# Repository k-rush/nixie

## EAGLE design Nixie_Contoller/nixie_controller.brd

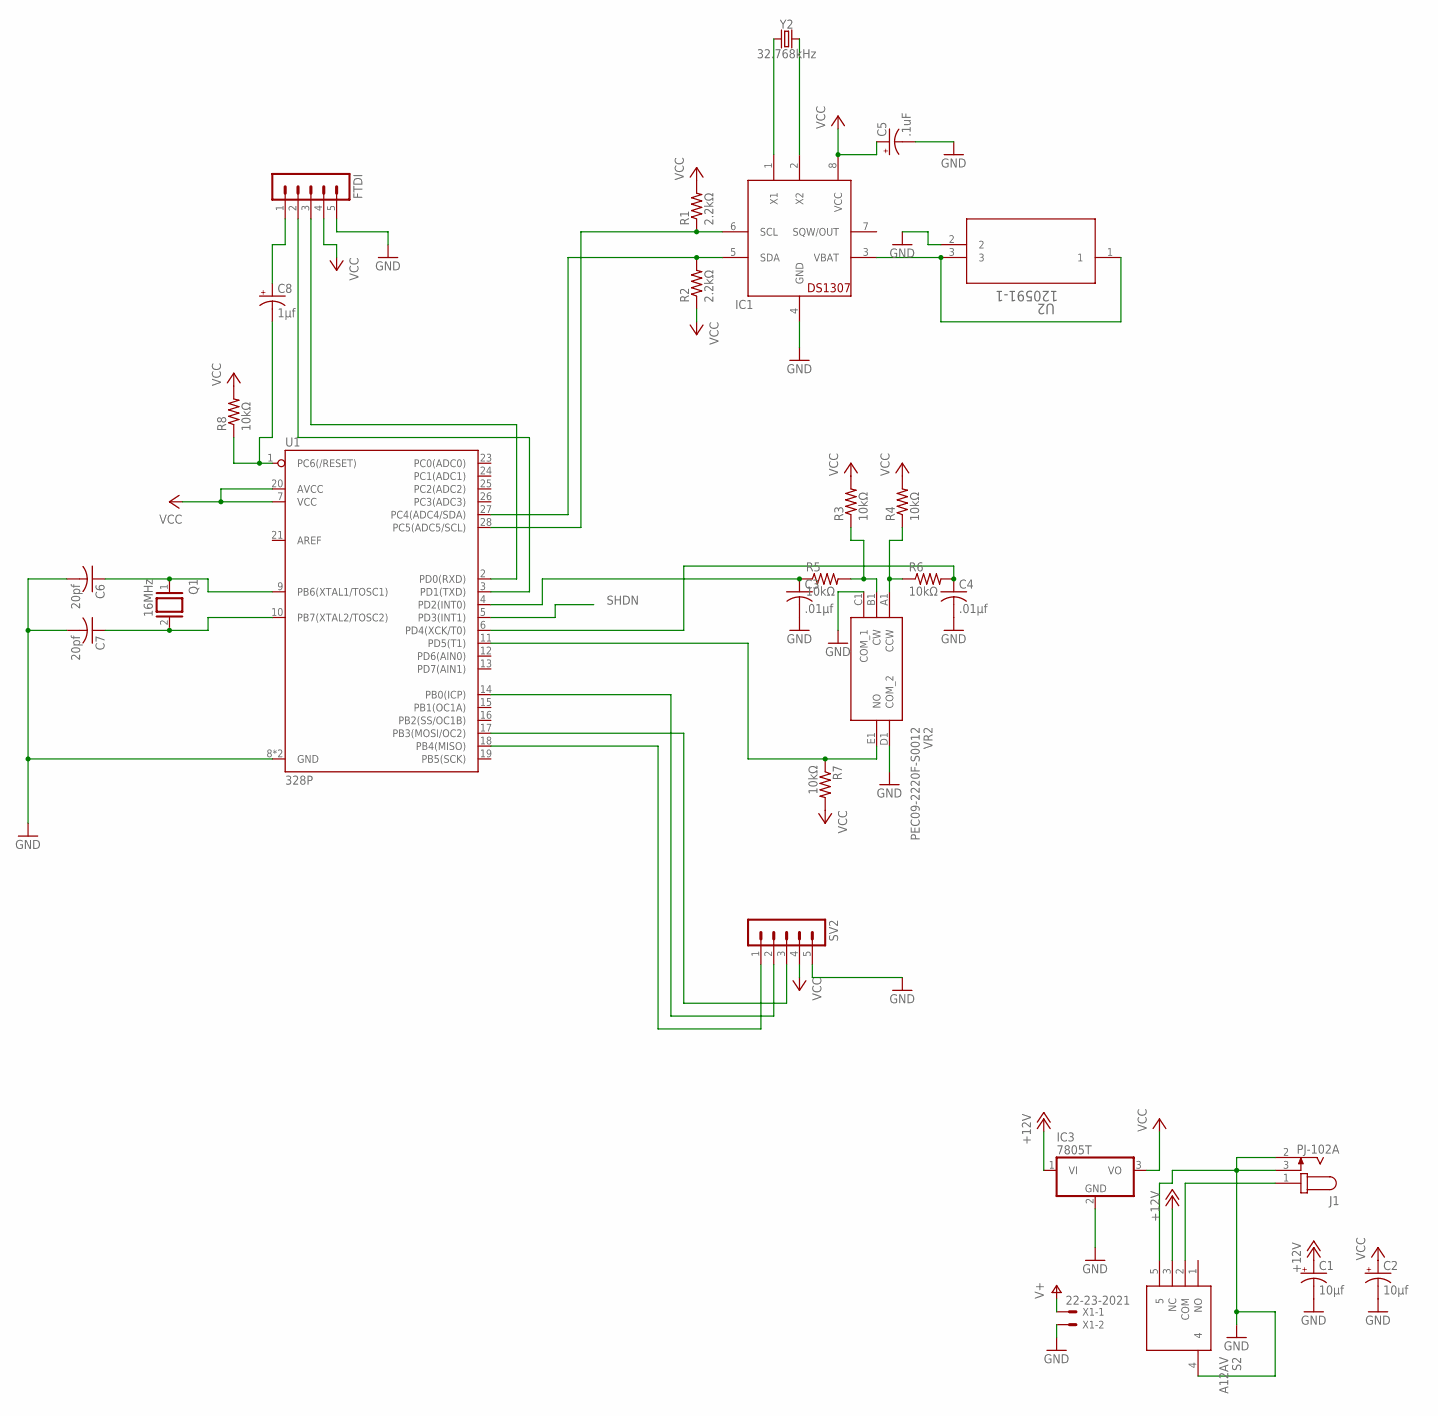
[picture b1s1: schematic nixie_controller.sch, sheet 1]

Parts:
C1, C2: 10μf; E2-5
C3, C4: .01μf; C050-030X075
C5: .1uF; E2-5
C6, C7: 20pf; C050-030X075
C8: 1μf; E2-5
FTDI: MA05-1
IC1: DS1307; DIL08
IC3: 7805T; TO220H
J1: PJ-102A; CUI_PJ-102A
Q1: 16MHz; QS
R1, R2: 2.2kΩ; 0207/10
R3, R4, R5, R6, R7, R8: 10kΩ; 0207/10
S2: A12AV
SV2: MA05-1
U1: 328P; DIP28
U2: 120591-1; CONN3_120591-1
VR2: PEC09-2220F-S0012; PEC092220FS0012
X1: 22-23-2021
Y2: 32.768kHz; CRYSTAL-PTH-2X6-CYL

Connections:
+12V: C1.+, IC3.1 (VI), S2.3 (NC); also elsewhere on the board
CLK: SV2.1, U1.18 (PB4(MISO))
GND: C1.-, C2.-, C3.2, C4.2, C5.-, C6.2, C7.2, FTDI.5, IC1.4 (GND), IC3.2 (GND), J1.2, J1.3, S2.4, S2.5, SV2.5, U1.8 (GND), U1.22 (GND), U2.2, VR2.C1 (COM_1), VR2.D1 (COM_2), X1.2; also elsewhere on the board
unnamed: IC1.3 (VBAT), U2.1, U2.3
unnamed: R7.1, U1.11 (PD5(T1)), VR2.E1 (NO)
unnamed: R4.1, R6.1, VR2.A1 (CCW)
unnamed: IC1.1 (X1), Y2.1
unnamed: IC1.2 (X2), Y2.2
unnamed: J1.1, S2.2 (COM)
unnamed: SV2.2, U1.14 (PB0(ICP))
unnamed: C3.1, R5.1, U1.4 (PD2(INT0))
unnamed: C4.1, R6.2, U1.6 (PD4(XCK/T0))
unnamed: C6.1, Q1.1, U1.9 (PB6(XTAL1/TOSC1))
unnamed: IC1.6 (SCL), R1.1, U1.28 (PC5(ADC5/SCL))
unnamed: IC1.5 (SDA), R2.2, U1.27 (PC4(ADC4/SDA))
unnamed: C8.-, R8.1, U1.1 (PC6(/RESET))
unnamed: R3.1, R5.2, VR2.B1 (CW)
unnamed: C7.1, Q1.2, U1.10 (PB7(XTAL2/TOSC2))
unnamed: C8.+, FTDI.1
unnamed: SV2.3, U1.17 (PB3(MOSI/OC2))
unnamed: FTDI.2, U1.3 (PD1(TXD))
unnamed: FTDI.3, U1.2 (PD0(RXD))
SHDN: U1.5 (PD3(INT1)); also elsewhere on the board
V+: X1.1; also elsewhere on the board
VCC: C2.+, C5.+, FTDI.4, IC1.8 (VCC), IC3.3 (VO), R1.2, R2.1, R3.2, R4.2, R7.2, R8.2, SV2.4, U1.7 (VCC), U1.20 (AVCC)

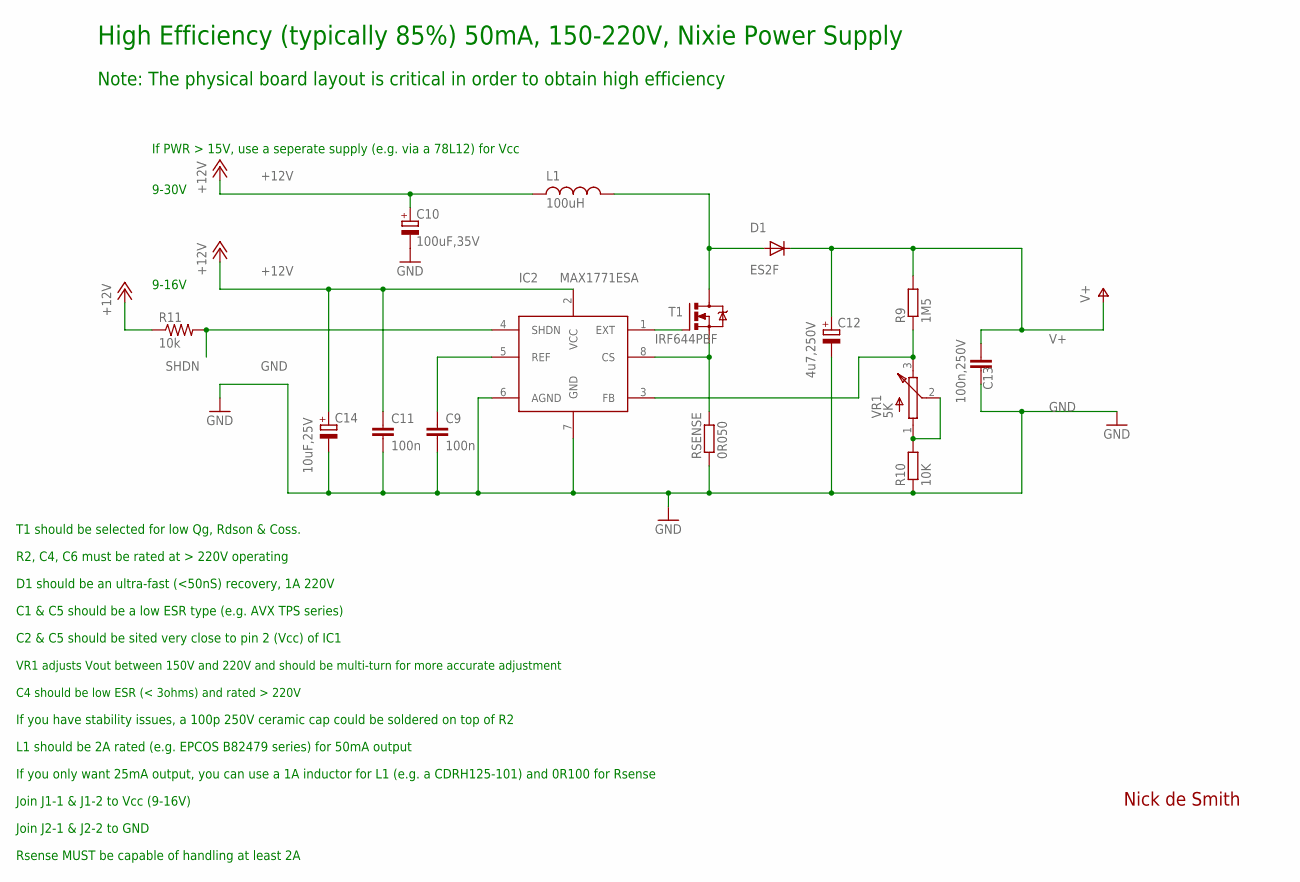
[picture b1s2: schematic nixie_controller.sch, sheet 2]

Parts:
C9, C11: 100n; C0805
C10: 100uF,35V; C-EIA-7343
C12: 4u7,250V; NICHICON-UJ-12
C13: 100n,250V; C2420
C14: 10uF,25V; C-EIA-7343
D1: ES2F; SMC
IC2: MAX1771ESA; SO-8
L1: 100uH; L-B82479
R9: 1M5; R2512
R10: 10K; R0805
R11: 10k; M0805
RSENSE: 0R050; R2010
T1: IRF644PBF; TO220BV
VR1: 5K; BOURNS-3214W

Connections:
+12V: C10.+, C11.1, C14.+, IC2.2 (VCC), L1.P$1 (1), R11.1; also elsewhere on the board
EXT: IC2.1 (EXT), T1.G
GND: C9.2, C10.-, C11.2, C12.1 (-), C13.P$2 (2), C14.-, IC2.6 (AGND), IC2.7 (GND), R10.1, RSENSE.1; also elsewhere on the board
unnamed: IC2.3 (FB), R9.1, VR1.3 (B)
unnamed: D1.A, L1.P$2 (2), T1.D
unnamed: C9.1, IC2.5 (REF)
unnamed: R10.2, VR1.1 (A), VR1.2 (W)
unnamed: IC2.8 (CS), RSENSE.2, T1.S
SHDN: IC2.4 (SHDN), R11.2; also elsewhere on the board
V+: C12.2 (+), C13.P$1 (1), D1.C, R9.2; also elsewhere on the board

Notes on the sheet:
R2, C4, C6 must be rated at > 220V operating
D1 should be an ultra-fast (<50nS) recovery, 1A 220V
C1 & C5 should be a low ESR type (e.g. AVX TPS series)
C2 & C5 should be sited very close to pin 2 (Vcc) of IC1
Nick de Smith
VR1 adjusts Vout between 150V and 220V and should be multi-turn for more accurate adjustment
C4 should be low ESR (< 3ohms) and rated > 220V
If you have stability issues, a 100p 250V ceramic cap could be soldered on top of R2
L1 should be 2A rated (e.g. EPCOS B82479 series) for 50mA output
Join J1-1 & J1-2 to Vcc (9-16V)
Join J2-1 & J2-2 to GND
T1 should be selected for low Qg, Rdson & Coss.
Rsense MUST be capable of handling at least 2A
High Efficiency (typically 85%) 50mA, 150-220V, Nixie Power Supply
9-16V
9-30V
If PWR > 15V, use a seperate supply (e.g. via a 78L12) for Vcc
Note: The physical board layout is critical in order to obtain high efficiency
If you only want 25mA output, you can use a 1A inductor for L1 (e.g. a CDRH125-101) and 0R100 for Rsense

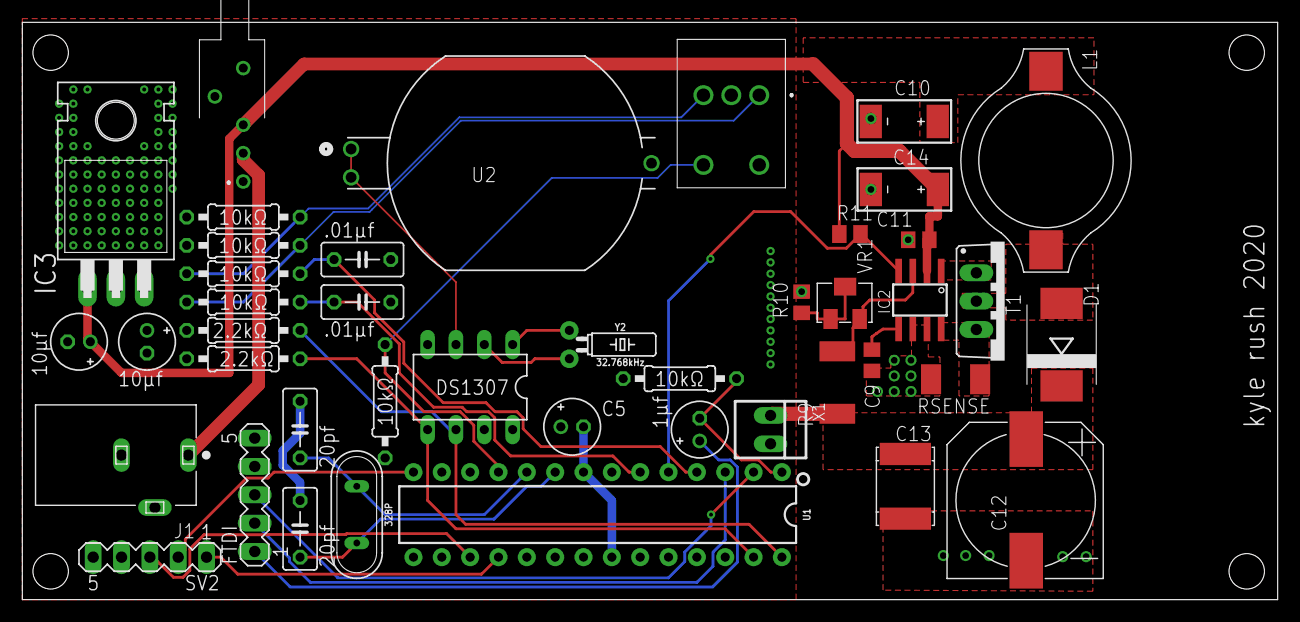
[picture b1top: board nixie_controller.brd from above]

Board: 2 copper layers, 112.5 x 51.7 mm, 43 parts (0 on the bottom side), 31 nets.

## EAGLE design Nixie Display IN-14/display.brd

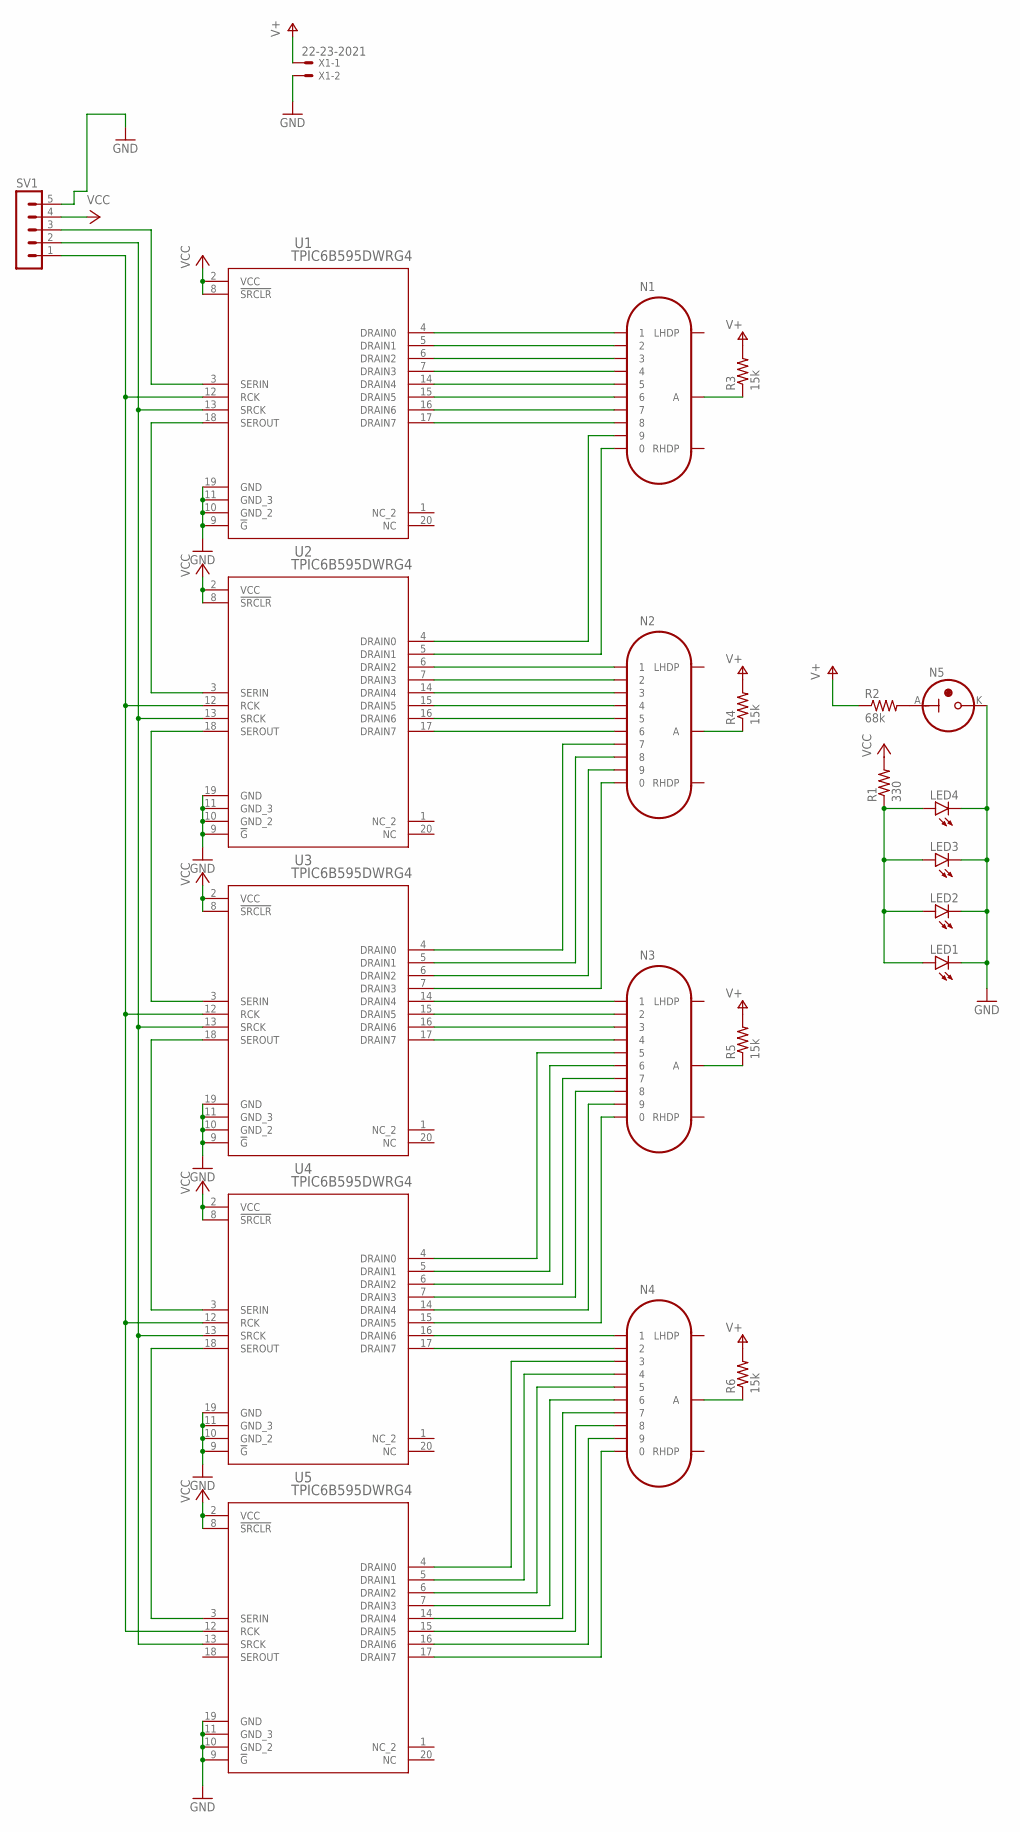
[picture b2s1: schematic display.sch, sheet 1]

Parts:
LED1, LED2, LED3, LED4: LED3MM
N1, N2, N3, N4: IN-14
N5: IN-3
R1: 330; R0805
R2: 68k; R0805
R3, R4, R5, R6: 15k; R0805
SV1: MA05-1
U1, U2, U3, U4, U5: TPIC6B595DWRG4; DW20
X1: 22-23-2021

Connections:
GND: LED1.K (C), LED2.K (C), LED3.K (C), LED4.K (C), N5.K, SV1.5, U1.9 (!G), U1.10 (GND_2), U1.11 (GND_3), U1.19 (GND), U2.9 (!G), U2.10 (GND_2), U2.11 (GND_3), U2.19 (GND), U3.9 (!G), U3.10 (GND_2), U3.11 (GND_3), U3.19 (GND), U4.9 (!G), U4.10 (GND_2), U4.11 (GND_3), U4.19 (GND), U5.9 (!G), U5.10 (GND_2), U5.11 (GND_3), U5.19 (GND), X1.2
unnamed: N1.1, U1.4 (DRAIN0)
unnamed: N1.2, U1.5 (DRAIN1)
unnamed: N1.3, U1.6 (DRAIN2)
unnamed: N1.4, U1.7 (DRAIN3)
unnamed: N1.5, U1.14 (DRAIN4)
unnamed: N1.6, U1.15 (DRAIN5)
unnamed: N1.7, U1.16 (DRAIN6)
unnamed: N1.8, U1.17 (DRAIN7)
unnamed: N1.9, U2.4 (DRAIN0)
unnamed: N1.0, U2.5 (DRAIN1)
unnamed: N2.1, U2.6 (DRAIN2)
unnamed: N2.2, U2.7 (DRAIN3)
unnamed: N2.3, U2.14 (DRAIN4)
unnamed: N2.4, U2.15 (DRAIN5)
unnamed: N2.5, U2.16 (DRAIN6)
unnamed: N2.6, U2.17 (DRAIN7)
unnamed: N2.7, U3.4 (DRAIN0)
unnamed: N2.8, U3.5 (DRAIN1)
unnamed: N2.9, U3.6 (DRAIN2)
unnamed: N2.0, U3.7 (DRAIN3)
unnamed: LED1.A, LED2.A, LED3.A, LED4.A, R1.1
unnamed: N5.A, R2.2
unnamed: N1.A, R3.1
unnamed: N2.A, R4.1
unnamed: N3.A, R5.1
unnamed: N4.A, R6.1
unnamed: U4.18 (SEROUT), U5.3 (SERIN)
unnamed: SV1.1, U1.12 (RCK), U2.12 (RCK), U3.12 (RCK), U4.12 (RCK), U5.12 (RCK)
unnamed: N3.1, U3.14 (DRAIN4)
unnamed: N3.2, U3.15 (DRAIN5)
unnamed: N3.3, U3.16 (DRAIN6)
unnamed: N3.4, U3.17 (DRAIN7)
unnamed: N3.8, U4.7 (DRAIN3)
unnamed: N3.6, U4.5 (DRAIN1)
unnamed: N3.9, U4.14 (DRAIN4)
unnamed: N3.5, U4.4 (DRAIN0)
unnamed: N3.7, U4.6 (DRAIN2)
unnamed: N3.0, U4.15 (DRAIN5)
unnamed: N4.1, U4.16 (DRAIN6)
unnamed: N4.2, U4.17 (DRAIN7)
unnamed: N4.0, U5.17 (DRAIN7)
unnamed: N4.9, U5.16 (DRAIN6)
unnamed: N4.8, U5.15 (DRAIN5)
unnamed: N4.7, U5.14 (DRAIN4)
unnamed: N4.6, U5.7 (DRAIN3)
unnamed: N4.5, U5.6 (DRAIN2)
unnamed: N4.4, U5.5 (DRAIN1)
unnamed: N4.3, U5.4 (DRAIN0)
unnamed: SV1.2, U1.13 (SRCK), U2.13 (SRCK), U3.13 (SRCK), U4.13 (SRCK), U5.13 (SRCK)
unnamed: SV1.3, U1.3 (SERIN)
unnamed: U1.18 (SEROUT), U2.3 (SERIN)
unnamed: U2.18 (SEROUT), U3.3 (SERIN)
unnamed: U3.18 (SEROUT), U4.3 (SERIN)
V+: R2.1, R3.2, R4.2, R5.2, R6.2, X1.1
VCC: R1.2, SV1.4, U1.2 (VCC), U1.8 (!SRCLR), U2.2 (VCC), U2.8 (!SRCLR), U3.2 (VCC), U3.8 (!SRCLR), U4.2 (VCC), U4.8 (!SRCLR), U5.2 (VCC), U5.8 (!SRCLR)

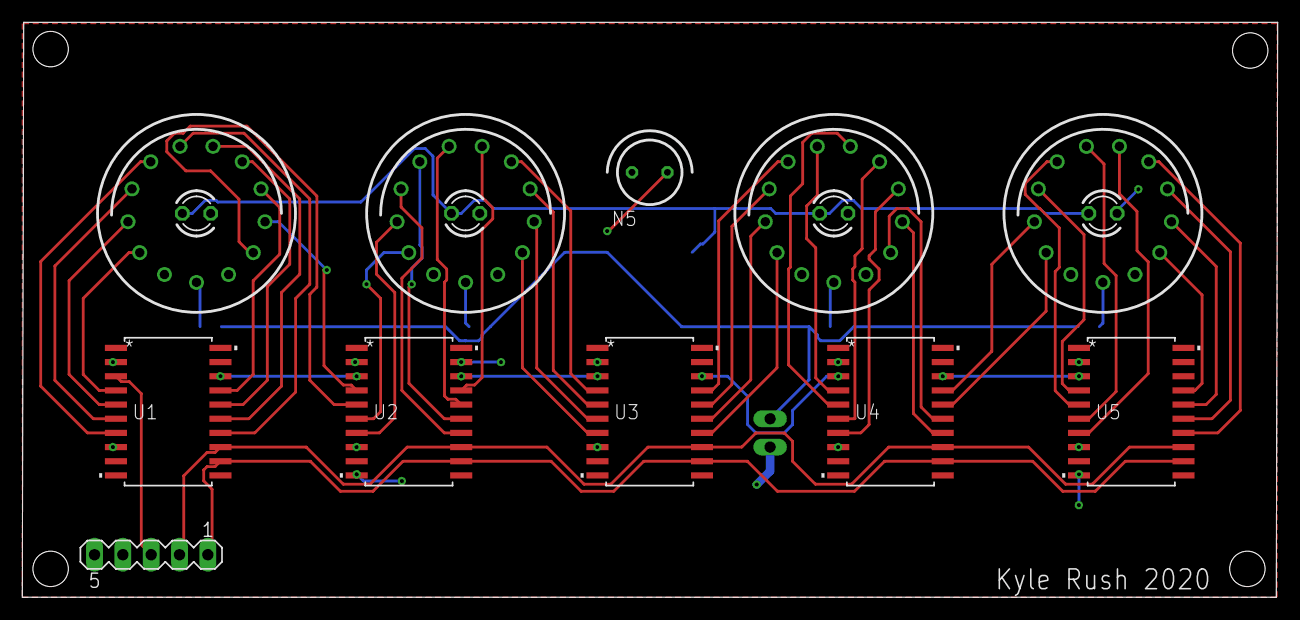
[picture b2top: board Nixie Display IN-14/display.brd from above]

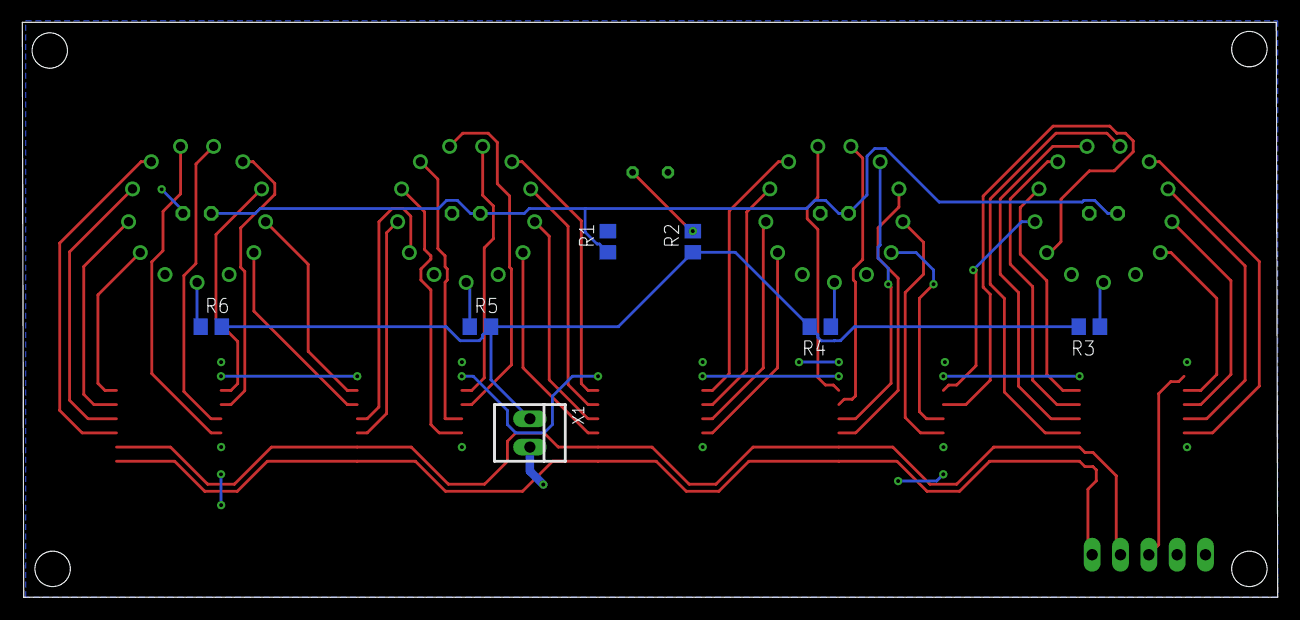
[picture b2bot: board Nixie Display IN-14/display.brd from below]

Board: 2 copper layers, 112.6 x 51.6 mm, 22 parts (7 on the bottom side), 56 nets.

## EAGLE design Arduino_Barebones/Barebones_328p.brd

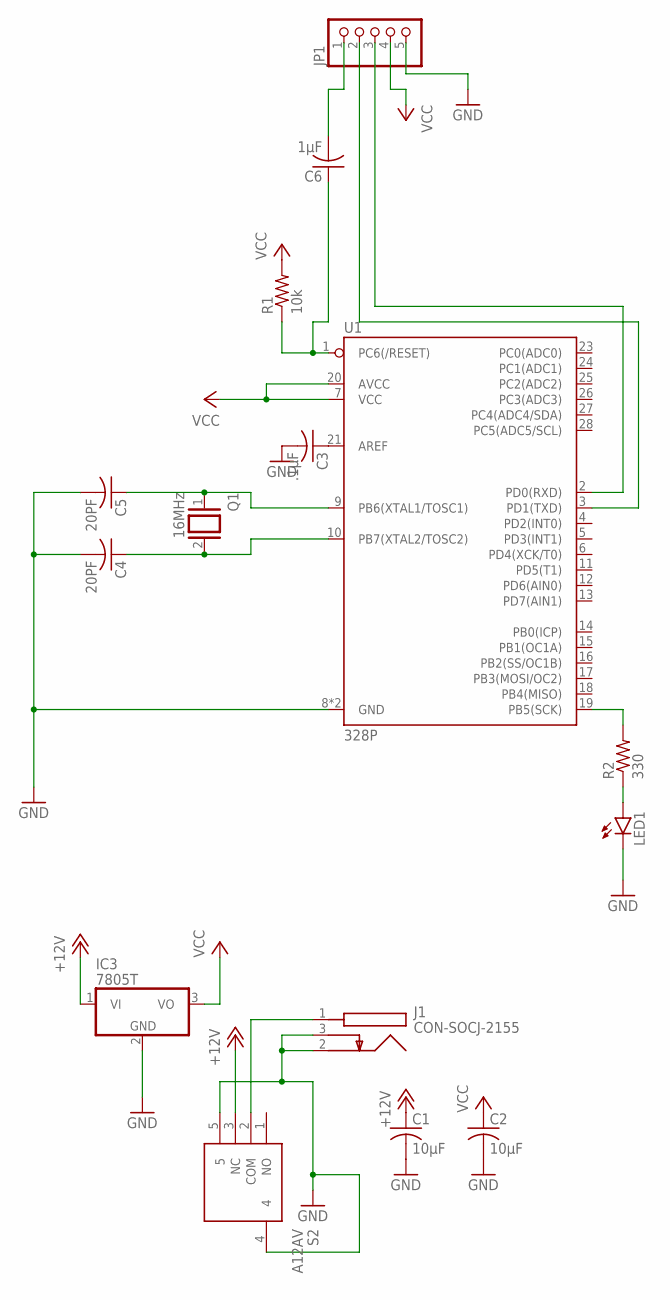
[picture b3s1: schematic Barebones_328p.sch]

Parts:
C1, C2: 10μF; C0603
C3: .1μF; C0603
C4, C5: 20PF; C0603
C6: 1μF; C0603
IC3: 7805T; TO220H
J1: CON-SOCJ-2155; CONSOCJ2155
JP1: PINHD-1X5; 1X05
LED1: LEDCHIP-LED0805; CHIP-LED0805
Q1: 16MHz; QS
R1: 10k; R0603
R2: 330; R0603
S2: A12AV
U1: 328P; DIP28

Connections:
+12V: C1.1, IC3.1 (VI), S2.3 (NC)
GND: C1.2, C2.2, C3.2, C4.2, C5.2, IC3.2 (GND), J1.2, J1.3, JP1.5, LED1.C, S2.4, S2.5, U1.8 (GND), U1.22 (GND)
unnamed: R2.2, U1.19 (PB5(SCK))
unnamed: LED1.A, R2.1
unnamed: J1.1, S2.2 (COM)
unnamed: C3.1, U1.21 (AREF)
unnamed: C5.1, Q1.1, U1.9 (PB6(XTAL1/TOSC1))
unnamed: C6.1, R1.1, U1.1 (PC6(/RESET))
unnamed: C4.1, Q1.2, U1.10 (PB7(XTAL2/TOSC2))
unnamed: C6.2, JP1.1
unnamed: JP1.2, U1.3 (PD1(TXD))
unnamed: JP1.3, U1.2 (PD0(RXD))
VCC: C2.1, IC3.3 (VO), JP1.4, R1.2, U1.7 (VCC), U1.20 (AVCC)

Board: 2 copper layers, 15 parts (0 on the bottom side), 13 nets, no tracks yet.

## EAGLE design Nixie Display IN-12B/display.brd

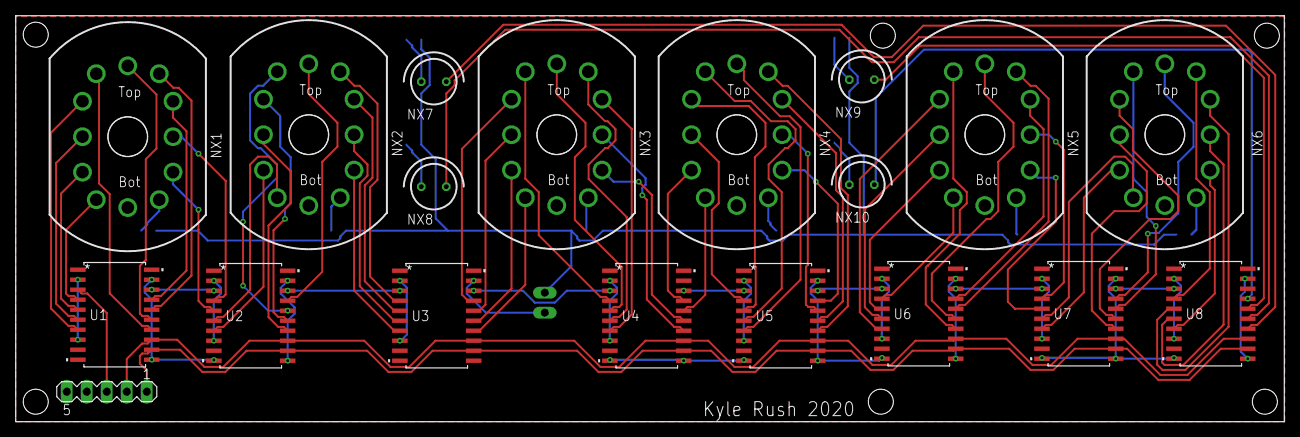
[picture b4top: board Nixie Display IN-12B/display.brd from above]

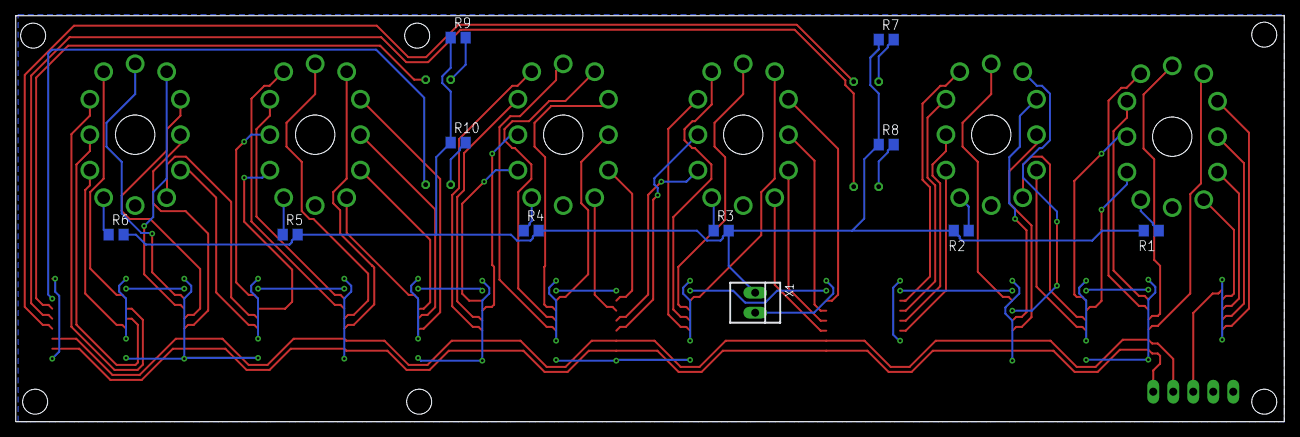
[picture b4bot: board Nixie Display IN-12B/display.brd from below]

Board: 2 copper layers, 161.1 x 51.6 mm, 30 parts (11 on the bottom side), 87 nets.

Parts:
NX1, NX2, NX3, NX4, NX5, NX6: IN-12-DSUB
NX7, NX8, NX9, NX10: IN-3
R1, R2, R3, R4, R5, R6: 15k; R0805
R7, R8, R9, R10: 68k; R0805
SV1: MA05-1
U1, U2, U3, U4, U5, U6, U7, U8: TPIC6B595DWRG4; DW20
X1: 22-23-2021

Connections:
GND: SV1.5, U1.9, U1.10, U1.11, U1.19, U2.9, U2.10, U2.11, U2.19, U3.9, U3.10, U3.11, U3.19, U4.9, U4.10, U4.11, U4.19, U5.9, U5.10, U5.11, U5.19, U6.9, U6.10, U6.11, U6.19, U7.9, U7.10, U7.11, U7.19, U8.9, U8.10, U8.11, U8.19, X1.2
unnamed: NX1.1, U1.4
unnamed: NX1.2, U1.5
unnamed: NX1.3, U1.6
unnamed: NX1.4, U1.7
unnamed: NX1.5, U1.14
unnamed: NX1.6, U1.15
unnamed: NX1.7, U1.16
unnamed: NX1.8, U1.17
unnamed: NX1.9, U2.4
unnamed: NX1.0, U2.5
unnamed: NX2.1, U2.6
unnamed: NX2.2, U2.7
unnamed: NX2.3, U2.14
unnamed: NX2.4, U2.15
unnamed: NX2.5, U2.16
unnamed: NX2.6, U2.17
unnamed: NX2.7, U3.4
unnamed: NX2.8, U3.5
unnamed: NX2.9, U3.6
unnamed: NX2.0, U3.7
unnamed: NX7.A, R7.2
unnamed: NX1.A, R1.1
unnamed: NX2.A, R2.1
unnamed: NX3.A, R3.1
unnamed: NX4.A, R4.1
unnamed: U4.18, U5.3
unnamed: SV1.1, U1.12, U2.12, U3.12, U4.12, U5.12, U6.12, U7.12, U8.12
unnamed: NX3.1, U3.14
unnamed: NX3.2, U3.15
unnamed: NX3.3, U3.16
unnamed: NX3.4, U3.17
unnamed: NX3.8, U4.7
unnamed: NX3.6, U4.5
unnamed: NX3.9, U4.14
unnamed: NX3.5, U4.4
unnamed: NX3.7, U4.6
unnamed: NX3.0, U4.15
unnamed: NX4.1, U4.16
unnamed: NX4.2, U4.17
unnamed: NX4.0, U5.17
unnamed: NX4.9, U5.16
unnamed: NX4.8, U5.15
unnamed: NX4.7, U5.14
unnamed: NX4.6, U5.7
unnamed: NX4.5, U5.6
unnamed: NX4.4, U5.5
unnamed: NX4.3, U5.4
unnamed: SV1.2, U1.13, U2.13, U3.13, U4.13, U5.13, U6.13, U7.13, U8.13
unnamed: U5.18, U6.3
unnamed: NX5.A, R5.1
unnamed: SV1.3, U1.3
unnamed: NX6.A, R6.1
unnamed: NX5.0, U7.5
unnamed: NX5.7, U6.16
unnamed: NX5.6, U6.15
unnamed: NX5.5, U6.14
unnamed: NX5.4, U6.7
unnamed: NX5.3, U6.6
unnamed: NX5.2, U6.5
unnamed: NX5.1, U6.4
unnamed: U6.18, U7.3
unnamed: NX5.8, U6.17
unnamed: NX5.9, U7.4
unnamed: U7.18, U8.3
unnamed: NX6.1, U7.6
unnamed: NX6.2, U7.7
unnamed: NX6.3, U7.14
unnamed: NX6.4, U7.15
unnamed: NX6.5, U7.16
unnamed: U1.18, U2.3
unnamed: U2.18, U3.3
unnamed: U3.18, U4.3
unnamed: NX6.6, U7.17
unnamed: NX6.7, U8.4
unnamed: NX6.8, U8.5
unnamed: NX6.9, U8.6
unnamed: NX6.0, U8.7
unnamed: NX8.A, R8.2
unnamed: NX9.A, R9.2
unnamed: NX10.A, R10.2
unnamed: NX7.K, U8.14
unnamed: NX8.K, U8.15
unnamed: NX9.K, U8.16
unnamed: NX10.K, U8.17
V+: R1.2, R2.2, R3.2, R4.2, R5.2, R6.2, R7.1, R8.1, R9.1, R10.1, X1.1
VCC: SV1.4, U1.2, U1.8, U2.2, U2.8, U3.2, U3.8, U4.2, U4.8, U5.2, U5.8, U6.2, U6.8, U7.2, U7.8, U8.2, U8.8

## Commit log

2019-12-19 init
2019-12-19 Adds schematics
2019-12-19 Changes to vertical mounted encoder and switch on base
2019-12-19 small big fixes
2019-12-24 Snapshot 12-23
2019-12-26 Adds LV switching PSU
2019-12-27 Revert "Adds LV switching PSU"
    This reverts commit 12f529c285d7cae732b9ac692bbbf0adcfd9615d.
2019-12-28 Shrinks board size, uses SMD components
2019-12-28 Snapshot 12/27
2019-12-31 Through hole, fixes HV PSU, all components
2020-01-27 Stable PSU, TPIC6b595 working. Release candidate
2020-01-28 Updates parts to Digikey equivalent, adds BOM, adds SHDN to pin 5
2020-01-28 Production ready board with BOMS
2020-01-29 Adds IN12B Display board
2020-02-01 Begins sketch, fixes spacing and encoder circuit
2020-02-01 Reverts encoder change
2020-02-05 Tweaks design, adds arduino clock sketch
2020-02-12 Reverses polarity of IN3
2020-02-24 Reconfigures controller, configures clock to pull sketch down SHDN pin

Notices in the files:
parts and their libraries:
SparkFun-IC-Microcontroller: Licensing: Creative Commons ShareAlike 4.0 International - https://creativecommons.org/licenses/by-sa/4.0
COPYRIGHT: Copyright (C) 2016 Accelerated Designs. All rights reserved
